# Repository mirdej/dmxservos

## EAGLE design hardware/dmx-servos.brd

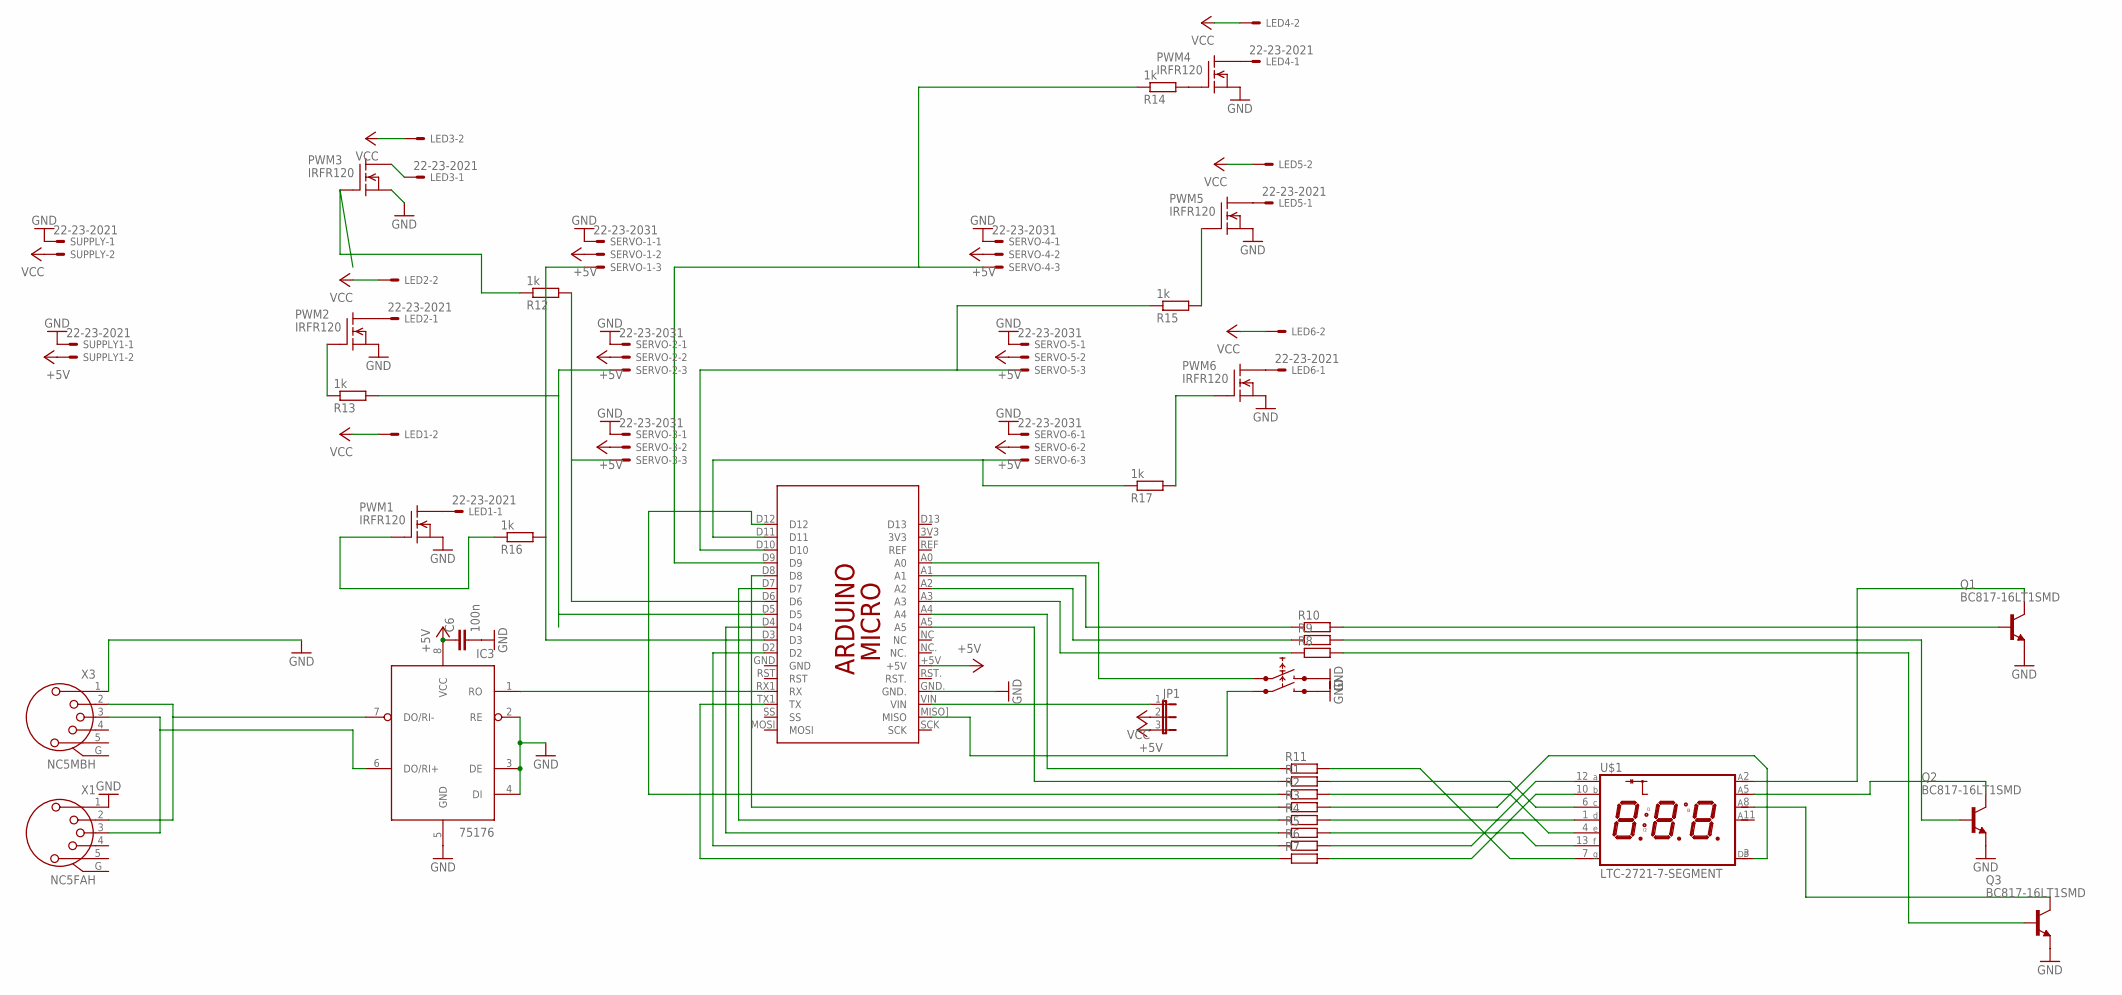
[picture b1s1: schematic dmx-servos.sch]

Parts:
C6: 100n; C0603
IC3: 75176; SO08
JP1: JP2E; JP2
LED1, LED2, LED3, LED4, LED5, LED6: 22-23-2021
PCB1: ARDUINO_MICRO
PWM1, PWM2, PWM3, PWM4, PWM5, PWM6: IRFR120; DPAK
Q1, Q2, Q3: BC817-16LT1SMD; SOT23-BEC
R1, R2, R3, R4, R5, R6, R7, R8, R9, R10, R11: R-EU_R1206; R1206
R12, R13, R14, R15, R16, R17: 1k; R1206
SERVO-1, SERVO-2, SERVO-3, SERVO-4, SERVO-5, SERVO-6: 22-23-2031
SUPPLY, SUPPLY1: 22-23-2021
U$1: LTC-2721-7-SEGMENT; LTC-2721
U$4, U$5: ALPS-TASTER-SKST
X1: NC5FAH
X3: NC5MBH

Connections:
+5V: C6.1, IC3.8 (VCC), JP1.3, PCB1.+5V, SERVO-1.2, SERVO-2.2, SERVO-3.2, SERVO-4.2, SERVO-5.2, SERVO-6.2, SUPPLY1.2
DMX2: IC3.7 (DO/RI-), X1.2, X3.2
DMX3: IC3.6 (DO/RI+), X1.3, X3.3
GND: C6.2, IC3.2 (RE), IC3.3 (DE), IC3.4 (DI), IC3.5 (GND), PCB1.GND., PWM1.3 (S), PWM2.3 (S), PWM3.3 (S), PWM4.3 (S), PWM5.3 (S), PWM6.3 (S), Q1.E, Q2.E, Q3.E, SERVO-1.1, SERVO-2.1, SERVO-3.1, SERVO-4.1, SERVO-5.1, SERVO-6.1, SUPPLY.1, SUPPLY1.1, U$4.P$2 (1), U$5.P$2 (1), X1.1, X3.1
unnamed: IC3.1 (RO), PCB1.RX1 (RX)
unnamed: PCB1.A0, U$5.P$1 (0)
unnamed: PCB1.D5, R13.2, SERVO-2.3
unnamed: PCB1.D3, R16.2, SERVO-1.3
unnamed: PCB1.D9, R14.1, SERVO-4.3
unnamed: PCB1.D10, R15.1, SERVO-5.3
unnamed: R7.2, U$1.10 (B)
unnamed: Q1.C, U$1.2 (D1)
unnamed: PCB1.D11, R17.1, SERVO-6.3
unnamed: PCB1.TX1 (TX), R7.1
unnamed: R6.2, U$1.12 (A)
unnamed: R5.2, U$1.13 (F)
unnamed: R4.2, U$1.1 (D)
unnamed: PCB1.D2, R6.1
unnamed: R2.2, U$1.4 (E)
unnamed: R1.2, U$1.6 (C)
unnamed: Q2.C, U$1.5 (D2)
unnamed: Q3.C, U$1.8 (D3)
unnamed: PCB1.D4, R5.1
unnamed: PCB1.D7, R4.1
unnamed: PCB1.D8, R3.1
unnamed: PCB1.D12, R2.1
unnamed: PCB1.A5, R1.1
unnamed: PCB1.A4, R11.1
unnamed: Q1.B, R10.2
unnamed: Q2.B, R9.2
unnamed: Q3.B, R8.2
unnamed: PCB1.A3, R8.1
unnamed: PCB1.A2, R9.1
unnamed: PCB1.A1, R10.1
unnamed: PCB1.MISO] (MISO), U$4.P$1 (0)
unnamed: PWM1.1 (G), R16.1
unnamed: LED1.1, PWM1.4 (D)
unnamed: LED2.1, PWM2.4 (D)
unnamed: JP1.1, PCB1.VIN
unnamed: LED3.1, PWM3.4 (D)
unnamed: LED4.1, PWM4.4 (D)
unnamed: LED5.1, PWM5.4 (D)
unnamed: LED6.1, PWM6.4 (D)
unnamed: PWM2.1 (G), R13.1
unnamed: PWM3.1 (G), R12.1
unnamed: PCB1.D6, R12.2, SERVO-3.3
unnamed: PWM5.1 (G), R15.2
unnamed: PWM6.1 (G), R17.2
unnamed: PWM4.1 (G), R14.2
unnamed: R3.2, U$1.3 (DP)
unnamed: R11.2, U$1.7 (G)
VCC: JP1.2, LED1.2, LED2.2, LED3.2, LED4.2, LED5.2, LED6.2, SUPPLY.2

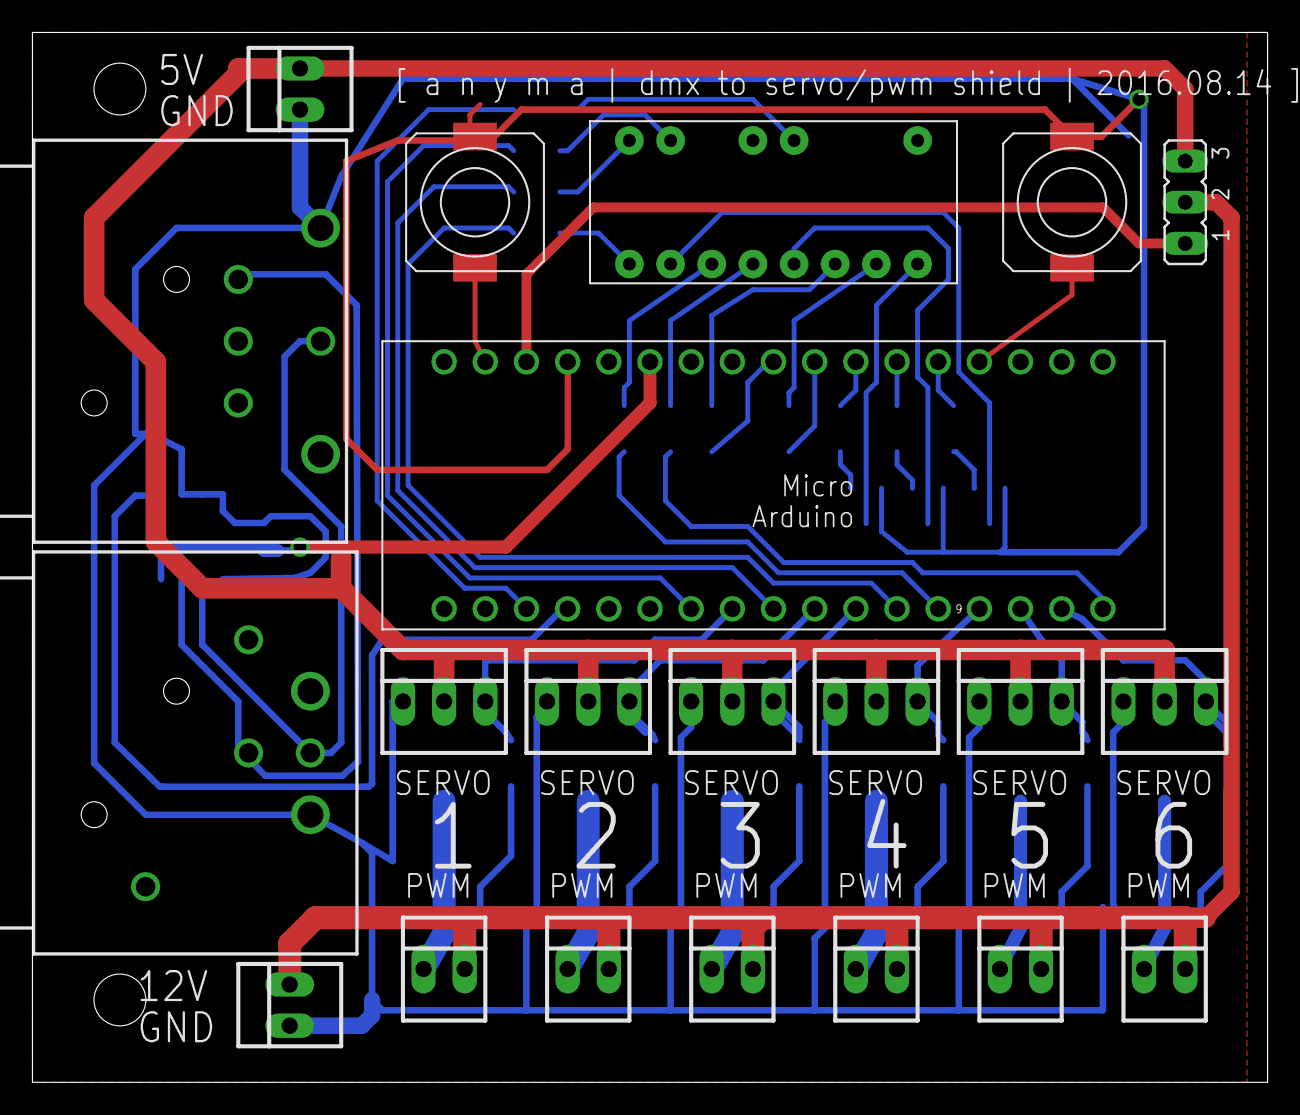
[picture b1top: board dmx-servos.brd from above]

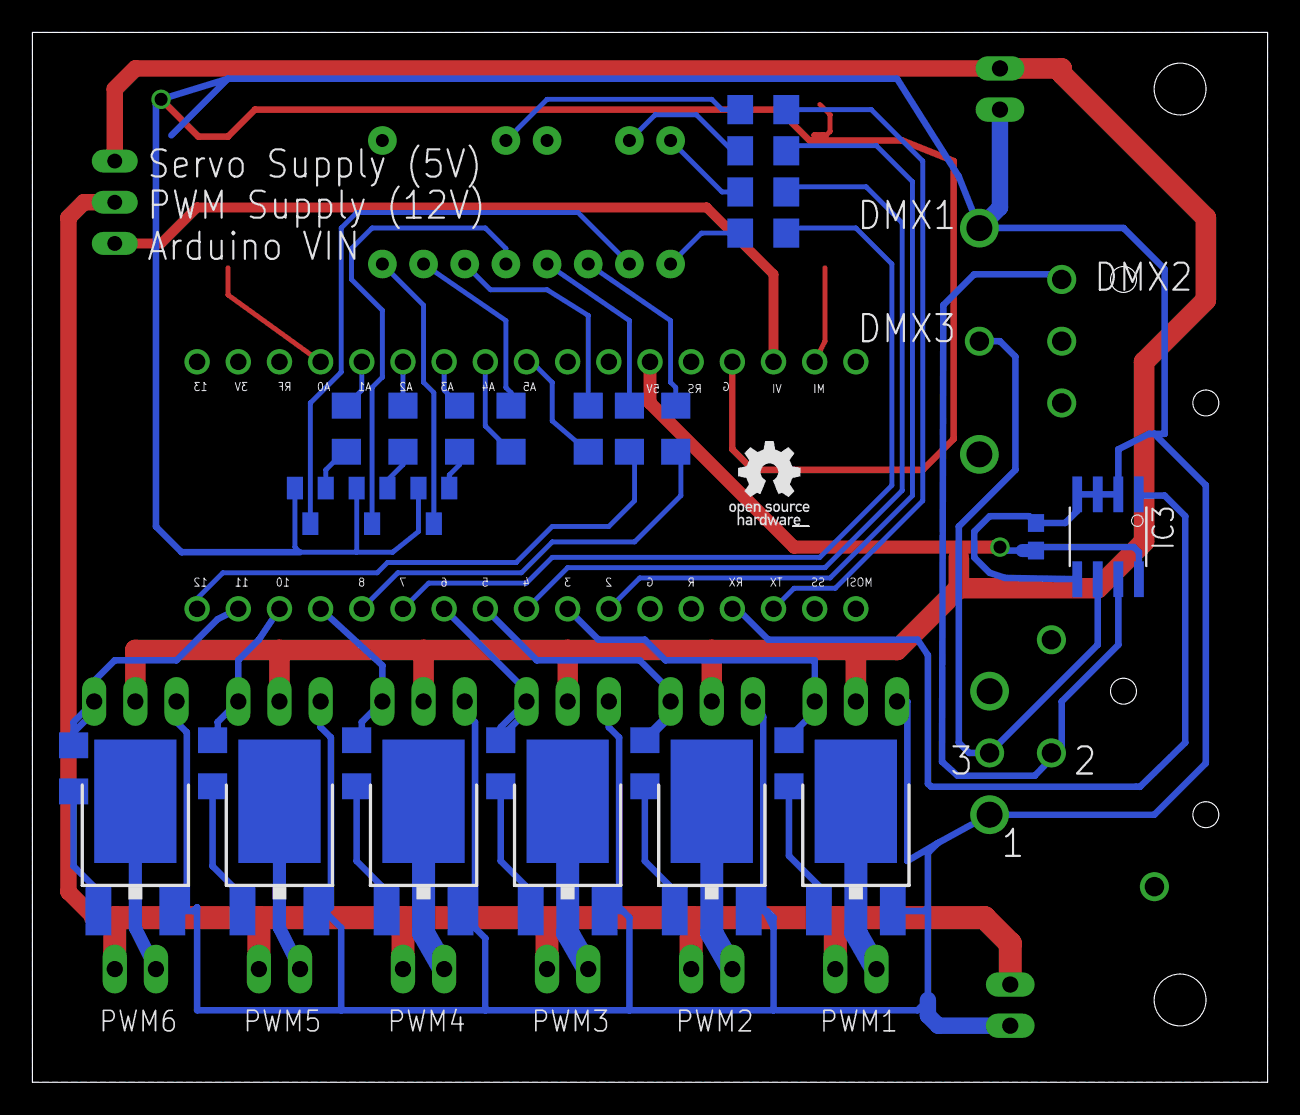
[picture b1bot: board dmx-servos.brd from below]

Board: 2 copper layers, 76.2 x 64.8 mm, 49 parts (28 on the bottom side), 52 nets.

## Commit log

2016-08-12 can set dmx address
2016-08-12 add board and schematic
2016-08-12 servos and pwm working
2016-08-12 freed up D13 for dmx-ready display
2016-08-17 in assignment in adjustable section
2016-08-17 in assignment in adjustable section. now for real
2016-08-23 double definition of out_pins
